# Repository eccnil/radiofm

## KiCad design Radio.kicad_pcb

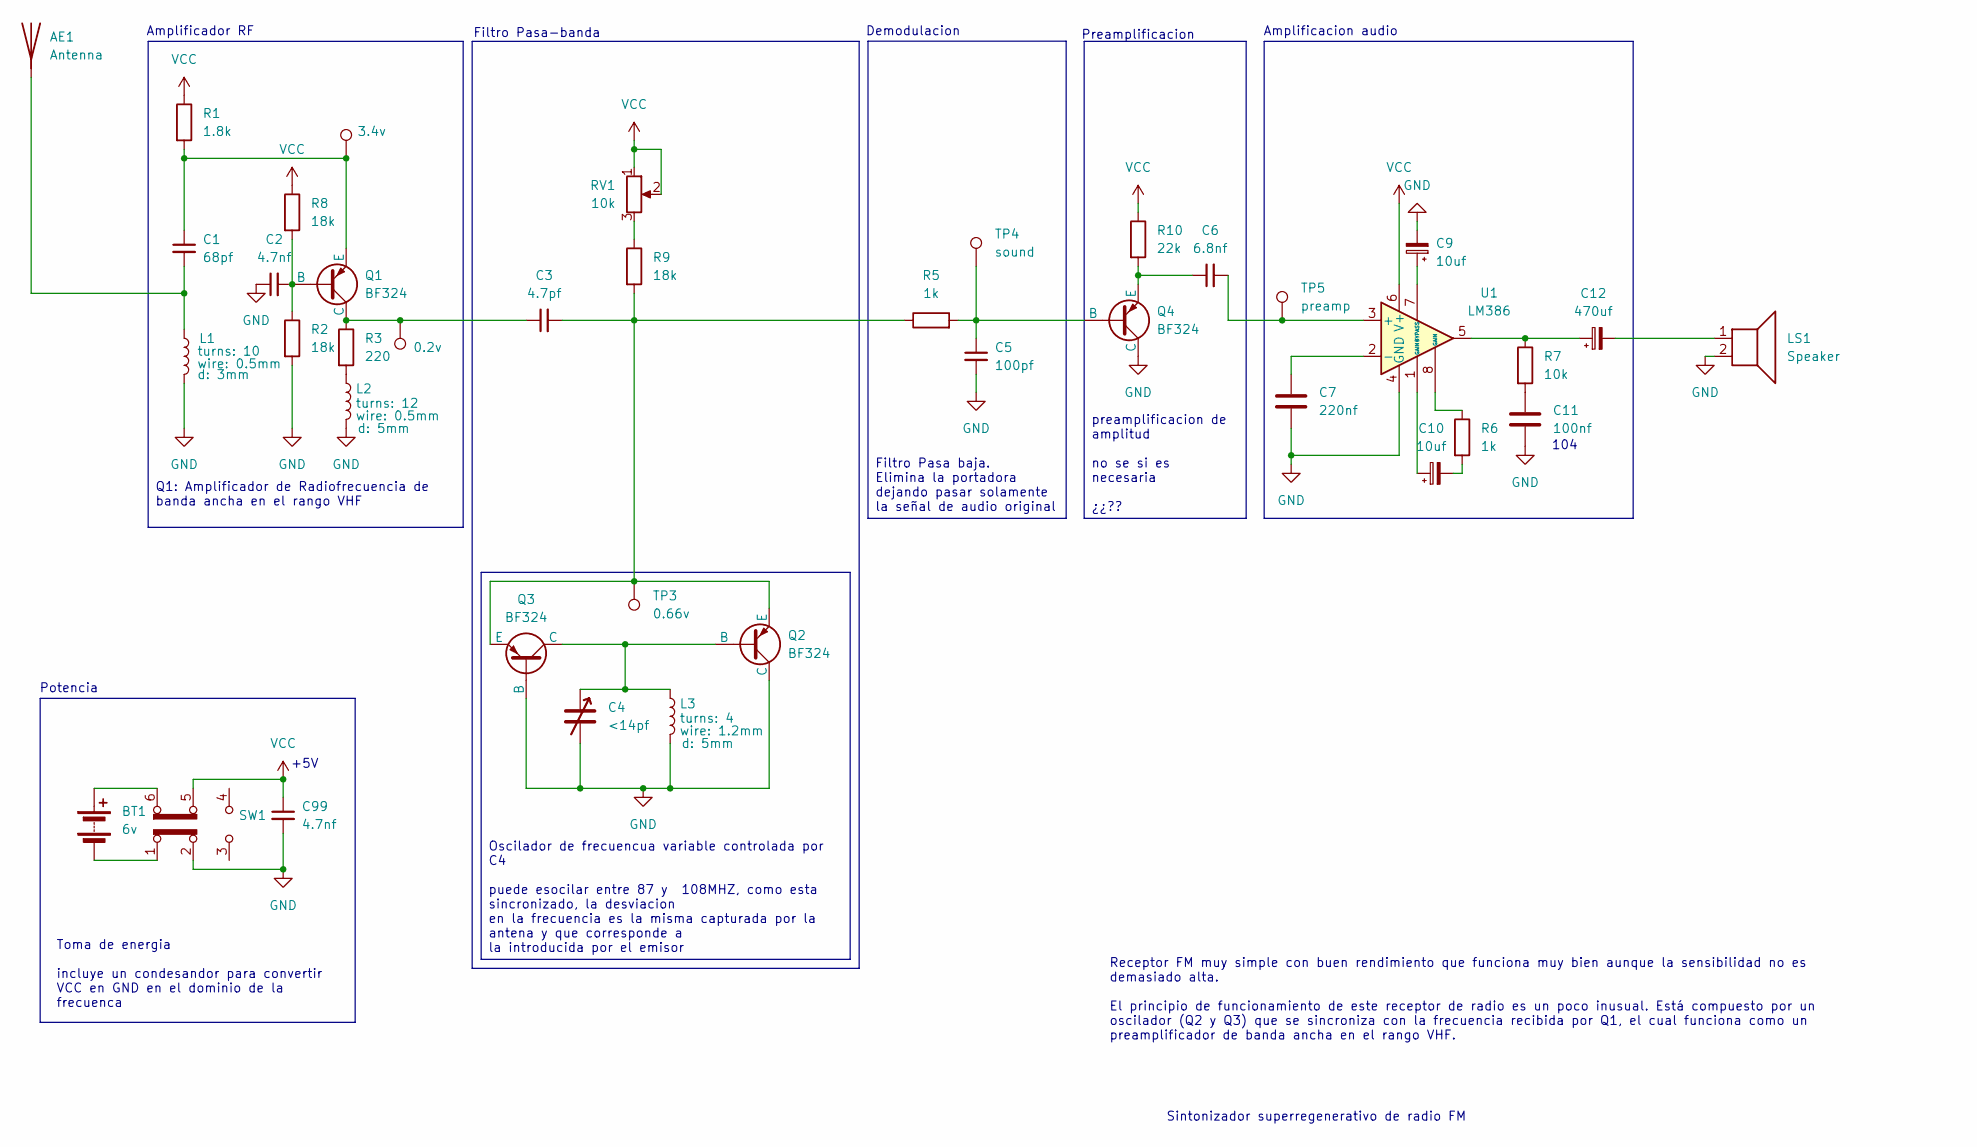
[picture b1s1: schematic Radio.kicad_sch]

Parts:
AE1: Antenna; Banana_Jack_1Pin
BT1: 6v; SolderWire-0.25sqmm_1x02_P4.5mm_D0.65mm_OD2mm_Relief
C1: 68pf; C_Disc_D5.0mm_W2.5mm_P5.00mm
C2: 4.7nf; C_Disc_D5.0mm_W2.5mm_P5.00mm
C3: 4.7pf; C_Disc_D5.0mm_W2.5mm_P5.00mm
C4: <14pf; CP_Elec_6.3x4.5
C5: 100pf; C_Disc_D5.0mm_W2.5mm_P5.00mm
C6: 6.8nf; C_Disc_D5.0mm_W2.5mm_P5.00mm
C7: 220nf; C_Disc_D7.5mm_W4.4mm_P5.00mm
C9, C10: 10uf; CP_Radial_D5.0mm_P2.50mm
C11: 100nf; C_Disc_D3.0mm_W2.0mm_P2.50mm
C12: 470uf; CP_Radial_D8.0mm_P3.80mm
C99: 4.7nf; C_Disc_D7.5mm_W4.4mm_P5.00mm
L1: 10 turns / 0.5mm SWG25 d = 3mm; L_Axial_L11.0mm_D4.5mm_P15.24mm_Horizontal_Fastron_MECC
L2: 12 turns / 0.5mm SWG25 d=5mm; L_Axial_L13.0mm_D4.5mm_P15.24mm_Horizontal_Fastron_HCCC
L3: 12 turns / 0.5mm SWG25 d=5mm; L_Axial_L9.5mm_D4.0mm_P12.70mm_Horizontal_Fastron_SMCC
LS1: Speaker; SolderWire-0.25sqmm_1x02_P4.5mm_D0.65mm_OD2mm_Relief
Q1, Q2, Q3, Q4: BF324; TO-92L_HandSolder
R1: 1.8k; R_Axial_DIN0207_L6.3mm_D2.5mm_P10.16mm_Horizontal
R2, R8, R9: 18k; R_1206_3216Metric_Pad1.30x1.75mm_HandSolder
R3: 220; R_Axial_DIN0207_L6.3mm_D2.5mm_P10.16mm_Horizontal
R5: 1k; R_1206_3216Metric_Pad1.30x1.75mm_HandSolder
R6: 1k; R_Axial_DIN0207_L6.3mm_D2.5mm_P5.08mm_Vertical
R7: 10k; R_Axial_DIN0207_L6.3mm_D2.5mm_P10.16mm_Horizontal
R10: 22k; R_Axial_DIN0207_L6.3mm_D2.5mm_P10.16mm_Horizontal
RV1: 10k; Potentiometer_Runtron_RM-065_Vertical
SW1: SW_Slide_DPDT; SW_Push_2P2T_Toggle_CK_PVA2OAH5xxxxxxV2
TP1: 3.4v; TestPoint_Pad_D2.0mm
TP2: 0.2v; TestPoint_Keystone_5019_Miniature
TP3: 0.66v; TestPoint_Keystone_5019_Miniature
TP4: sound; TestPoint_Keystone_5019_Miniature
TP5: preamp; TestPoint_Keystone_5019_Miniature
U1: LM386; DIP-8_W7.62mm_LongPads

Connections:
GND: C2.1, C4.2, C5.2, C7.1, C9.2, C11.2, C99.2, L1.2, L2.2, L3.2, LS1.2, Q2.1 (C), Q3.2 (B), Q4.1 (C), R2.2, SW1.2 (B), U1.4 (GND)
unnamed: AE1.1 (A), C1.2, L1.1
unnamed: BT1.1 (+), SW1.6 (C)
unnamed: BT1.2 (-), SW1.1 (A)
unnamed: C10.1, U1.1 (GAIN)
unnamed: C10.2, R6.2
unnamed: C11.1, R7.2
unnamed: C12.1, R7.1, U1.5
unnamed: C12.2, LS1.1
unnamed: L2.1, R3.2
unnamed: C2.2, Q1.2 (B), R2.1, R8.2
unnamed: C3.1, Q1.1 (C), R3.1, TP2.1
unnamed: C1.1, Q1.3 (E), R1.2, TP1.1
unnamed: C4.1, L3.1, Q2.2 (B), Q3.1 (C)
unnamed: C3.2, Q2.3 (E), Q3.3 (E), R5.1, R9.2, TP3.1
unnamed: C5.1, Q4.2 (B), R5.2, TP4.1
unnamed: C6.1, Q4.3 (E), R10.2
unnamed: R6.1, U1.8 (GAIN)
unnamed: R9.1, RV1.3
unnamed: C6.2, TP5.1, U1.3 (+)
unnamed: C7.2, U1.2 (-)
unnamed: C9.1, U1.7 (BYPASS)
VCC: C99.1, R1.1, R8.1, R10.1, RV1.1, RV1.2, SW1.5 (B), U1.6 (V+)

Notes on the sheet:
Sintonizador superregenerativo de radio FM
104
Amplificacion audio
Filtro Pasa-banda
+5V
Amplificador RF
Preamplificacion
Demodulacion
Potencia
Q1: Amplificador de Radiofrecuencia de banda ancha en el rango VHF
Toma de energia incluye un condesandor para convertir VCC en GND en el dominio de la frecuenca
Oscilador de frecuencua variable controlada por C4 puede esocilar entre 87 y 108MHZ, como esta sincronizado, la desviacion en la frecuencia es la misma capturada por la antena y que corresponde a la introducida por el emisor
Receptor FM muy simple con buen rendimiento que funciona muy bien aunque la sensibilidad no es demasiado alta. El principio de funcionamiento de este receptor de radio es un poco inusual. Está compuesto por un oscilador (Q2 y Q3) que se sincroniza con la frecuencia recibida por Q1, el cual funciona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
preamplificacion de amplitud no se si es necesaria ¿¿??
Filtro Pasa baja. Elimina la portadora dejando pasar solamente la señal de audio original

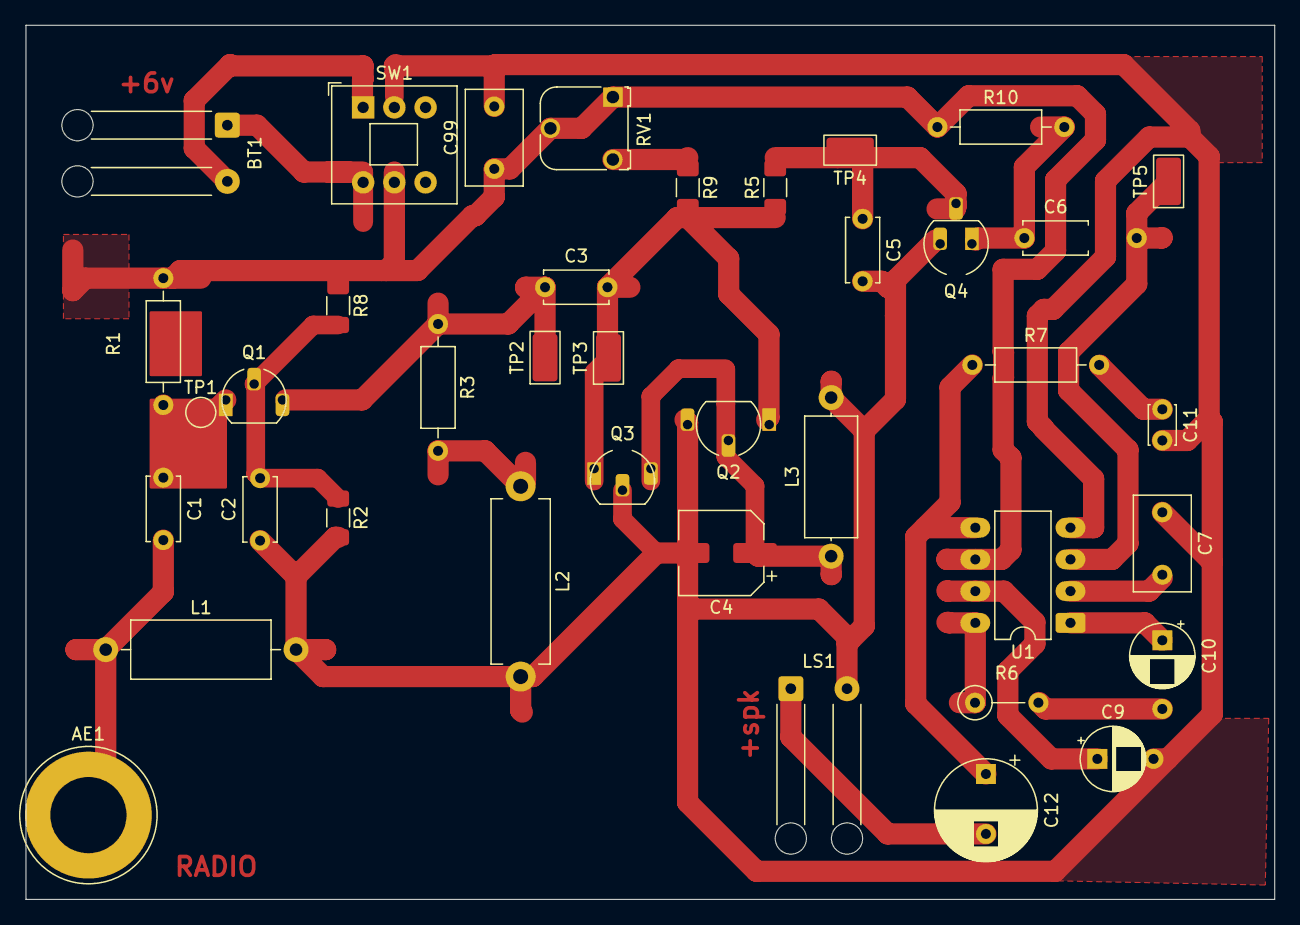
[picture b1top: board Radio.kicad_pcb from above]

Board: 2 copper layers, 100.0 x 70.0 mm, 39 parts (0 on the bottom side), 23 nets.

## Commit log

2025-06-10 pocket radio
2025-06-10 gitignore
2025-06-10 new schema
2025-06-12 Revert "new schema"
    This reverts commit 4b47ae0ea03e86690386e7109dba345f2f4c1c6c.
